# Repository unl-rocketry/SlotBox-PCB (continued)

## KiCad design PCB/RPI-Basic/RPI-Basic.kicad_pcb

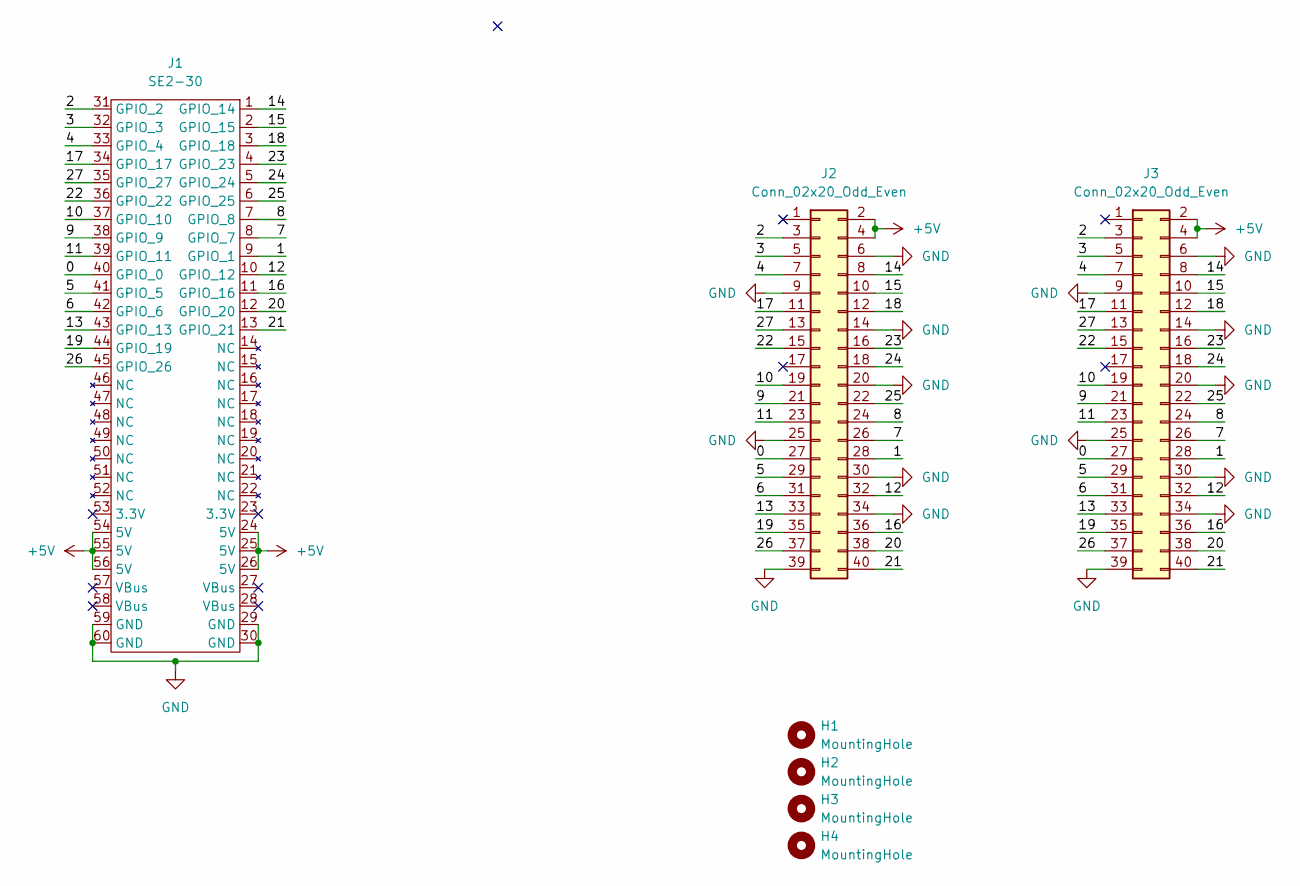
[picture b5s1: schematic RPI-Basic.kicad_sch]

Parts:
H1, H2, H3, H4: MountingHole; MountingHole_2.2mm_M2
J1: SE2-30
J2, J3: Conn_02x20_Odd_Even; PinHeader_2x20_P2.54mm_Vertical

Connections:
+5V: J1.24 (5V), J1.25 (5V), J1.26 (5V), J1.54 (5V), J1.55 (5V), J1.56 (5V), J2.2, J2.4, J3.2, J3.4
/0: J1.40 (GPIO_0), J2.27, J3.27
/1: J1.9 (GPIO_1), J2.28, J3.28
/2: J1.31 (GPIO_2), J2.3, J3.3
/3: J1.32 (GPIO_3), J2.5, J3.5
/4: J1.33 (GPIO_4), J2.7, J3.7
/5: J1.41 (GPIO_5), J2.29, J3.29
/6: J1.42 (GPIO_6), J2.31, J3.31
/7: J1.8 (GPIO_7), J2.26, J3.26
/8: J1.7 (GPIO_8), J2.24, J3.24
/9: J1.38 (GPIO_9), J2.21, J3.21
/10: J1.37 (GPIO_10), J2.19, J3.19
/11: J1.39 (GPIO_11), J2.23, J3.23
/12: J1.10 (GPIO_12), J2.32, J3.32
/13: J1.43 (GPIO_13), J2.33, J3.33
/14: J1.1 (GPIO_14), J2.8, J3.8
/15: J1.2 (GPIO_15), J2.10, J3.10
/16: J1.11 (GPIO_16), J2.36, J3.36
/17: J1.34 (GPIO_17), J2.11, J3.11
/18: J1.3 (GPIO_18), J2.12, J3.12
/19: J1.44 (GPIO_19), J2.35, J3.35
/20: J1.12 (GPIO_20), J2.38, J3.38
/21: J1.13 (GPIO_21), J2.40, J3.40
/22: J1.36 (GPIO_22), J2.15, J3.15
/23: J1.4 (GPIO_23), J2.16, J3.16
/24: J1.5 (GPIO_24), J2.18, J3.18
/25: J1.6 (GPIO_25), J2.22, J3.22
/26: J1.45 (GPIO_26), J2.37, J3.37
/27: J1.35 (GPIO_27), J2.13, J3.13
GND: J1.29 (GND), J1.30 (GND), J1.59 (GND), J1.60 (GND), J2.6, J2.9, J2.14, J2.20, J2.25, J2.30, J2.34, J2.39, J3.6, J3.9, J3.14, J3.20, J3.25, J3.30, J3.34, J3.39

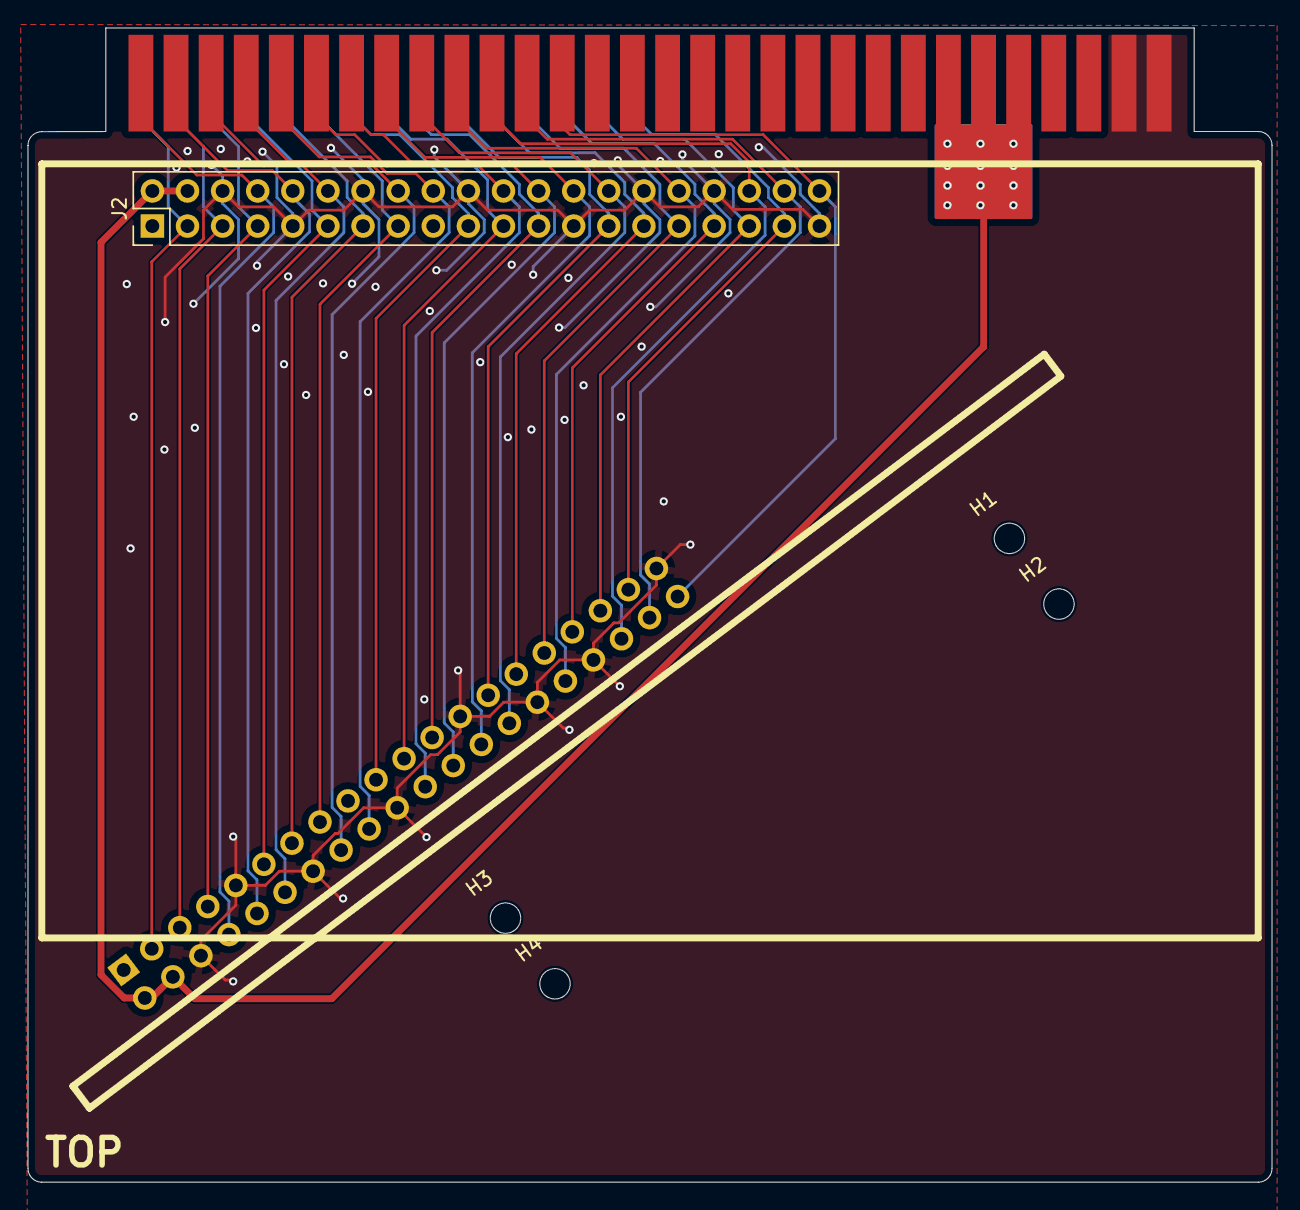
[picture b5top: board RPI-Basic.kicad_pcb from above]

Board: 2 copper layers, 90.0 x 83.5 mm, 7 parts (1 on the bottom side), 30 nets.

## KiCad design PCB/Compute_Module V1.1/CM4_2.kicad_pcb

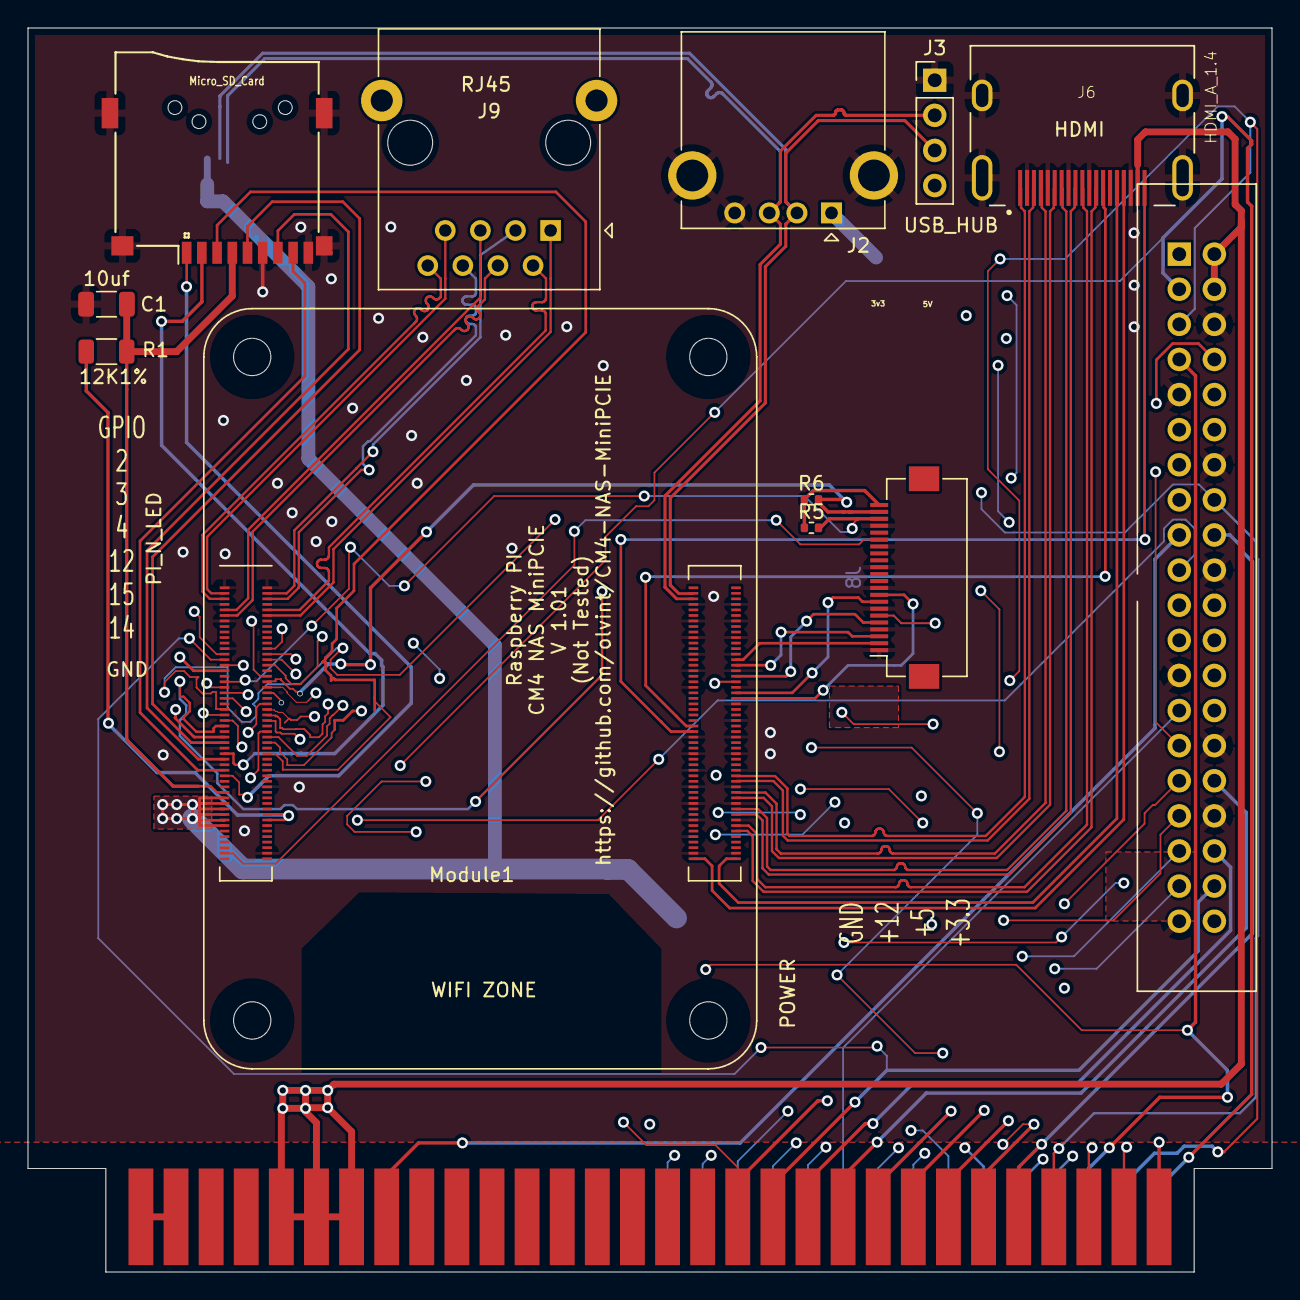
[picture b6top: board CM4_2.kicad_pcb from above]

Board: 4 copper layers, 90.0 x 90.0 mm, 14 parts (1 on the bottom side), 74 nets.

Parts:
C1: 10uf; C_1206_3216Metric
J1: SE2-30
J2: USB_A; USB_A_CONNFLY_DS1095-WNR0
J3: USB_HUB; PinHeader_1x04_P2.54mm_Vertical
J4: USB_B_Micro; USB_Mini-B_Lumberg_2486_01_Horizontal
J5: Micro_SD_Card; Conn_uSDcard
J6: HDMI_A_1.4; EDAC 690-019-298-412
J8: Conn_01x22_Female; Hirose_FH12-22S-0.5SH_1x22-1MP_P0.50mm_Horizontal
J9: RJ45; RJ45_Ninigi_GE
K4: RASPBERRY_PI4_HEADER
Module1: ComputeModule4-CM4; Raspberry-Pi-4-Compute-Module
R1: 12K1%; R_1206_3216Metric
R5, R6: 2.2K 1%; R_0402_1005Metric

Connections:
1.8V_CM4: Module1.88 (+1.8v_(Output)), Module1.90 (+1.8v_(Output))
3.3V_CM4: Module1.84 (+3.3v_(Output)), Module1.86 (+3.3v_(Output)), R1.1
3V3: J1.23 (3.3V), J1.53 (3.3V), K4.1 (3V3), K4.17 (3V3)
5V_CM4: Module1.77 (+5v_(Input)), Module1.79 (+5v_(Input)), Module1.81 (+5v_(Input)), Module1.83 (+5v_(Input)), Module1.85 (+5v_(Input)), Module1.87 (+5v_(Input))
+5V_USB: J2.1 (VBUS), J3.4
/0: J1.40 (GPIO_0), K4.27 (GPIO0)
/1: J1.9 (GPIO_1), K4.28 (GPIO1)
/4: J1.33 (GPIO_4), K4.7 (GPIO4), Module1.54 (GPIO4)
/5: J1.41 (GPIO_5), K4.29 (GPIO5), Module1.34 (GPIO5)
/5V: J1.24 (5V), J1.25 (5V), J1.26 (5V), J1.54 (5V), J1.55 (5V), J1.56 (5V), J6.18 (+5V), K4.2 (5V), K4.4 (5V)
/6: J1.42 (GPIO_6), K4.31 (GPIO6), Module1.30 (GPIO6)
/7: J1.8 (GPIO_7), K4.26 (GPIO7), Module1.37 (GPIO7)
/8: J1.7 (GPIO_8), K4.24 (GPIO8), Module1.39 (GPIO8)
/9: J1.38 (GPIO_9), K4.21 (GPIO9), Module1.40 (GPIO9)
/10: J1.37 (GPIO_10), K4.19 (GPIO10), Module1.44 (GPIO10)
/11: J1.39 (GPIO_11), K4.23 (GPIO11), Module1.38 (GPIO11)
/12: J1.10 (GPIO_12), K4.32 (GPIO12), Module1.31 (GPIO12)
/13: J1.43 (GPIO_13), K4.33 (GPIO13), Module1.28 (GPIO13)
/14: J1.1 (GPIO_14), K4.8 (GPIO14), Module1.55 (GPIO14)
/15: J1.2 (GPIO_15), K4.10 (GPIO15), Module1.51 (GPIO15)
/16: J1.11 (GPIO_16), K4.36 (GPIO16), Module1.29 (GPIO16)
/17: J1.34 (GPIO_17), K4.11 (GPIO17), Module1.50 (GPIO17)
/18: J1.3 (GPIO_18), K4.12 (GPIO18), Module1.49 (GPIO18)
/19: J1.44 (GPIO_19), K4.35 (GPIO19), Module1.26 (GPIO19)
/20: J1.12 (GPIO_20), K4.38 (GPIO20), Module1.27 (GPIO20)
/21: J1.13 (GPIO_21), K4.40 (GPIO21), Module1.25 (GPIO21)
/22: J1.36 (GPIO_22), K4.15 (GPIO22), Module1.46 (GPIO22)
/23: J1.4 (GPIO_23), K4.16 (GPIO23), Module1.47 (GPIO23)
/24: J1.5 (GPIO_24), K4.18 (GPIO24), Module1.45 (GPIO24)
/25: J1.6 (GPIO_25), K4.22 (GPIO25), Module1.41 (GPIO25)
/26: J1.45 (GPIO_26), K4.37 (GPIO26), Module1.24 (GPIO26)
/27: J1.35 (GPIO_27), K4.13 (GPIO27), Module1.48 (GPIO27)
/+3.3v: J8.22, R5.1, R6.1
/CAM0_C_N: J8.8, Module1.140 (CAM0_C_N)
/CAM0_C_P: J8.9, Module1.142 (CAM0_C_P)
/CAM0_D0_N: J8.2, Module1.128 (CAM0_D0_N)
/CAM0_D0_P: J8.3, Module1.130 (CAM0_D0_P)
/CAM0_D1_N: J8.5, Module1.134 (CAM0_D1_N)
/CAM0_D1_P: J8.6, Module1.136 (CAM0_D1_P)
/CAM_GPIO: J8.17, Module1.97 (Camera_GPIO)
/Eth_P0_N: J9.2, Module1.10 (Ethernet_Pair0_N)
/Eth_P0_P: J9.1, Module1.12 (Ethernet_Pair0_P)
/Eth_P1_N: J9.6, Module1.6 (Ethernet_Pair1_N)
/Eth_P1_P: J9.3, Module1.4 (Ethernet_Pair1_P)
/Eth_P2_N: J9.5, Module1.9 (Ethernet_Pair2_N)
/Eth_P2_P: J9.4, Module1.11 (Ethernet_Pair2_P)
/Eth_P3_N: J9.8, Module1.5 (Ethernet_Pair3_N)
/Eth_P3_P: J9.7, Module1.3 (Ethernet_Pair3_P)
/HDMI0_CEC: J6.13 (CEC), Module1.151 (HDMI0_CEC)
/HDMI0_CLK_N: J6.12 (CK-), Module1.190 (HDMI0_CLK_N)
/HDMI0_CLK_P: J6.10 (CK+), Module1.188 (HDMI0_CLK_P)
/HDMI0_HOTPLUG: J6.19 (HPD/HEAC-), Module1.153 (HDMI0_HOTPLUG)
/HDMI0_SCL: J6.15 (SCL), Module1.200 (HDMI0_SCL)
/HDMI0_SDA: J6.16 (SDA), Module1.199 (HDMI0_SDA)
/HDMI0_TX0_N: J6.9 (D0-), Module1.184 (HDMI0_TX0_N)
/HDMI0_TX0_P: J6.7 (D0+), Module1.182 (HDMI0_TX0_P)
/HDMI0_TX1_N: J6.6 (D1-), Module1.178 (HDMI0_TX1_N)
/HDMI0_TX1_P: J6.4 (D1+), Module1.176 (HDMI0_TX1_P)
/HDMI0_TX2_N: J6.3 (D2-), Module1.172 (HDMI0_TX2_N)
/HDMI0_TX2_P: J6.1 (D2+), Module1.170 (HDMI0_TX2_P)
/ID_SC: J8.20, Module1.35 (ID_SC), R5.2
/ID_SD: J8.21, Module1.36 (ID_SD), R6.2
/SD_CLK: J5.5 (CLK), Module1.57 (SD_CLK)
/SD_CMD: J5.3 (CMD), Module1.62 (SD_CMD)
/SD_DAT0: J5.7 (DAT0), Module1.63 (SD_DAT0)
/SD_DAT1: J5.8 (DAT1), Module1.67 (SD_DAT1)
/SD_DAT2: J5.1 (DAT2), Module1.69 (SD_DAT2)
/SD_DAT3: J5.2 (DAT3/CD), Module1.61 (SD_DAT3)
/SD_PWR_ON: C1.1, J5.4 (VDD), Module1.75 (SD_PWR_ON), R1.2
/USB2_N: J2.2 (D-), J3.3, J4.2 (D-), Module1.103 (USB2_N)
/USB2_P: J2.3 (D+), J3.2, J4.3 (D+), Module1.105 (USB2_P)
GND: C1.2, J1.29 (GND), J1.30 (GND), J1.59 (GND), J1.60 (GND), J2.4 (GND), J2.5 (Shield), J3.1, J4.5 (GND), J4.6 (Shield), J5.6 (VSS), J5.9 (SHIELD), J6.2 (D2S), J6.5 (D1S), J6.8 (D0S), J6.11 (CKS), J6.17 (GND), J6.SH1 (SH), J6.SH2 (SH), J6.SH3 (SH), J6.SH4 (SH), J8.1, J8.4, J8.7, J8.10, J8.13, J8.16, J8.19, K4.6 (GND), K4.9 (GND), K4.14 (GND), K4.20 (GND), K4.25 (GND), K4.30 (GND), K4.34 (GND), K4.39 (GND), Module1.1 (GND), Module1.2 (GND), Module1.7 (GND), Module1.8 (GND), Module1.13 (GND), Module1.14 (GND), Module1.22 (GND), Module1.23 (GND), Module1.32 (GND), Module1.33 (GND), Module1.42 (GND), Module1.43 (GND), Module1.52 (GND), Module1.53 (GND), Module1.59 (GND), Module1.60 (GND), Module1.65 (GND), Module1.66 (GND), Module1.71 (GND), Module1.74 (GND), Module1.98 (GND), Module1.107 (GND), Module1.108 (GND), Module1.113 (GND), Module1.114 (GND), Module1.119 (GND), Module1.120 (GND), Module1.125 (GND), Module1.126 (GND), Module1.131 (GND), Module1.132 (GND), Module1.137 (GND), Module1.138 (GND), Module1.144 (GND), Module1.150 (GND), Module1.155 (GND), Module1.156 (GND), Module1.161 (GND), Module1.162 (GND), Module1.167 (GND), Module1.168 (GND), Module1.173 (GND), Module1.174 (GND), Module1.179 (GND), Module1.180 (GND), Module1.185 (GND), Module1.186 (GND), Module1.191 (GND), Module1.192 (GND), Module1.197 (GND), Module1.198 (GND)
SCL: J1.32 (GPIO_3), K4.5 (GPIO3), Module1.56 (GPIO3)
SDA: J1.31 (GPIO_2), K4.3 (GPIO2), Module1.58 (GPIO2)

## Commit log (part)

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2026-01-27 power schematic
2026-01-29 Added gitignore
2026-01-29 preliminary battery board schematic and pcb design
    Author: yetiodo <verybluebluejay@gmail.com>
2026-02-01 changed battery config to series, added graphic
2026-02-03 Compute_module PCB files added
    temp work
2026-02-03 helpful stuff
2026-02-05 preliminary sensor board schematics and pcb layout
2026-02-12 Added Module
    Added Ult. GPS Breakout V3
2026-02-12 Comlpeted power board schematic
2026-02-13 make look nice
2026-02-16 CM4 Small
    test
2026-02-16 cm4 small
2026-02-16 dont remember what all is in this commit
2026-02-26 Name and new thingy
    Changed the name a couple of times and new branch called Backplane
2026-02-26 added SE2-30 edge connector footprint with full board cutout
2026-02-26 Backplane connectors
    Got the labeling on the connectors done, just the connecting needs to be done
2026-02-26 palced RFD in schematic and layout
2026-02-26 Initial PCB layout.
2026-02-28 Connector Symbol
2026-02-28 Updated power regulator to add SSR to output for switching 24v off
2026-02-28 added connector
2026-02-28 fixed connector symbol
2026-02-28 routed all traces to connector
2026-02-28 forgot to save
2026-02-28 added connector and started layout
2026-02-28 added connector to schematic
2026-02-28 added 24v connector and wired connector
2026-02-28 Wired Layout
2026-02-28 added keep-out zone for connector, added logo to back
2026-02-28 small edits
2026-03-01 Removed unused symbol file, updated board layout footprint
2026-03-01 edge cuts! thanks G2
2026-03-01 Updated backplane and removed unused connectors
2026-03-01 updated footprint from lib
2026-03-01 assigned footprints to capacitors, preliminary placement of components on pcb
2026-03-05 40pin
2026-03-05 3/4 almost done
2026-03-08 added design rules
2026-03-08 connected all components and ran DRC with no errors
2026-03-08 Finished new backplane
2026-03-08 added gnd vias to ensure better conductivity between gnd planes
2026-03-08 added PCBway DRU
2026-03-08 edited trace widths and moved some stuff
2026-03-09 Improved power rail layout and added silkscreen, added teardrops
2026-03-09 Touched up spacing to make it exact
2026-03-10 update schematics
2026-03-10 update footprints
2026-03-10 removed old Power reg board
2026-03-10 progress
2026-03-10 removed 2.2 and fixed DRU
2026-03-10 updated Footprint to include polygon in pin
2026-03-10 added test points
2026-03-10 added switch footprint
2026-03-11 Rounded edges of main board footprint, added TOP and BOTTOM
2026-03-11 added connector and switch
2026-03-11 Fixed DRC error
2026-03-11 removed old cm4 board and updated footprint on all boards
2026-03-11 initial work on basic Pi board
2026-03-12 layed out board
2026-03-12 removed cm4 board
2026-03-12 added forgotten member whoops
2026-03-12 added support mounting
2026-03-12 Updated to match proper depth
2026-03-12 Moved board total length to 83.51mm
2026-03-12 edits from meeting
2026-03-12 Fixed layout not aligning properly
2026-03-12 updated board footprint and rerouted
2026-03-12 Added ideal diode to battery board, cleaned up battery board layout
2026-03-12 Added better labeling to backplane connectors
2026-03-14 Made board thinner by 1.5mm, removed reference identifier on back artwork
2026-03-15 Updated gitignore for fabrication outputs
